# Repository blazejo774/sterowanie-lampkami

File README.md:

# 🔴🟢🔵 Sterowanie Lampkami Choinkowymi

Projekt ma sterować serią diod LED, poprzez zmienianie ustawień diód na jedno z wielu ustawień, z których użytkownik może wybrać przystosowane dla niego oświetlenie. Projekt zaweria różne rodzaje oświetlenia, miedzy innymi:

- [ ] Oscylacja światełek czerwonych, zielonych lub niebieskich.
- [ ] Włączenie bądź wyłączenie poszczególnych kolorów.
- [ ] Inne niestandardowe ustawienia oświetlenia.

Można rozszerzyć ilość używanych diod, poprzez dodanie więcej gałęzi po 3 diody:
 - Zamiast 1 gałęzi z 3 diodami, tworzysz np. 7 równoległych gałęzi po 3 diody w szeregu.
 - Każda gałąź dostaje swój rezystor, np. 7 rezystorów po 120Ω dla zielonych LED-ów.
 - MOSFET steruje wszystkimi 7 gałęziami naraz.
 
👉 Zalety: Nie zmienia się napięcie, MOSFET łatwo steruje większą ilością diod.

## 📝 Dokumentacja

ℹ Kod → [**Dokumentacja**](https://github.com/blazejo774/sterowanie-lampkami/blob/d19fd1ce32649a07414ba25e057f50cffe792c03/%5BCODE%5D/main.c)

ℹ Wykaz elementów → [**Dokumentacja**](https://github.com/blazejo774/sterowanie-lampkami/blob/d19fd1ce32649a07414ba25e057f50cffe792c03/%5BELECTRONICS%5D/readme.md)

## ⭐ Software

💾 Kod → [**main.c**](https://github.com/blazejo774/sterowanie-lampkami/blob/d19fd1ce32649a07414ba25e057f50cffe792c03/%5BCODE%5D/main.c)

## 💡 Hardware

💾 Schemat Elektryczny → [**Schemat Elektryczny**](https://github.com/blazejo774/sterowanie-lampkami/blob/d19fd1ce32649a07414ba25e057f50cffe792c03/%5BELECTRONICS%5D/scheme.pdf)

💾 Schemat Płytki PCB TOP → [**Płytka-TOP**](https://github.com/blazejo774/sterowanie-lampkami/blob/d19fd1ce32649a07414ba25e057f50cffe792c03/%5BBOARD%5D/Board_TOP.pdf)

💾 Schemat Płytki PCB BOTTOM → [**Płytka-BOTTOM**](https://github.com/blazejo774/sterowanie-lampkami/blob/d19fd1ce32649a07414ba25e057f50cffe792c03/%5BBOARD%5D/Board_BOTTOM.pdf)

💾 Schemat Płytki PCB(IMAGE) → [**Płytka**](https://github.com/blazejo774/sterowanie-lampkami/blob/d19fd1ce32649a07414ba25e057f50cffe792c03/%5BBOARD%5D/BOARD.png)

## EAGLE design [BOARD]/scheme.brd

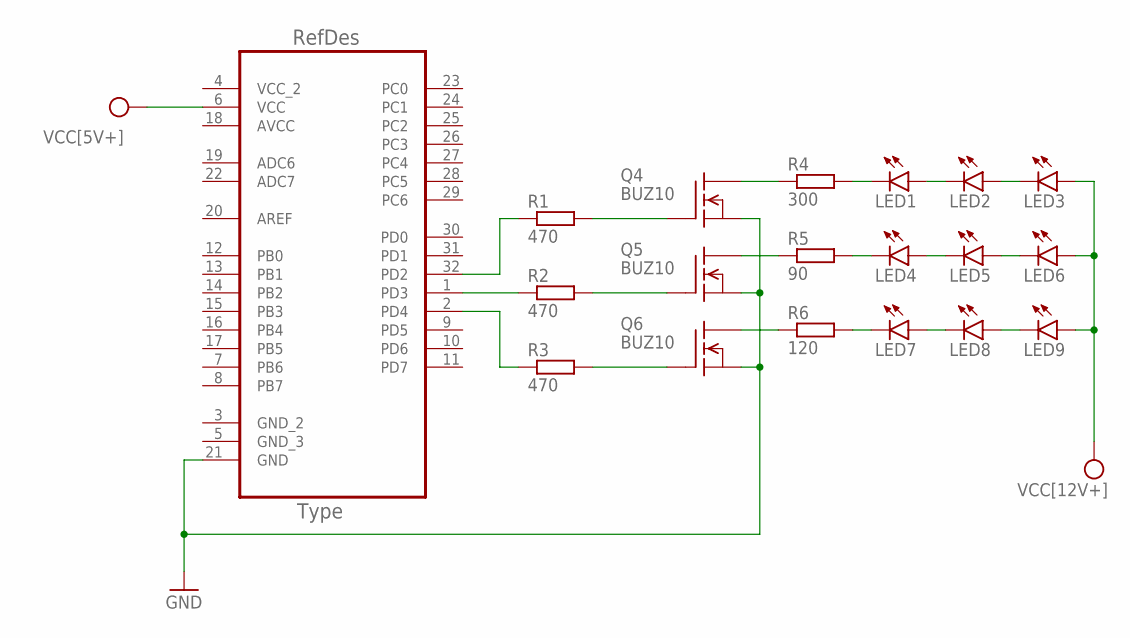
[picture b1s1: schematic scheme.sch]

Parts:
LED1, LED2, LED3, LED4, LED5, LED6, LED7, LED8, LED9: LED5MM
Q4, Q5, Q6: BUZ10; TO220
R1, R2, R3: 470; 0204/7
R4: 300; 0204/7
R5: 90; 0204/7
R6: 120; 0204/7
U2: ATMEGA328P-AU; QFP80P900X900X120-32N

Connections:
AVCC: U2.18 (AVCC)
GND: Q4.3 (S), Q5.3 (S), Q6.3 (S), U2.21 (GND)
unnamed: LED4.K (C), R5.2
unnamed: LED4.A, LED5.K (C)
unnamed: LED1.K (C), R4.2
unnamed: LED1.A, LED2.K (C)
unnamed: LED2.A, LED3.K (C)
unnamed: LED5.A, LED6.K (C)
unnamed: LED7.K (C), R6.2
unnamed: LED7.A, LED8.K (C)
unnamed: LED8.A, LED9.K (C)
unnamed: Q6.2 (D), R6.1
unnamed: Q5.2 (D), R5.1
unnamed: Q4.2 (D), R4.1
unnamed: Q4.1 (G), R1.2
unnamed: Q5.1 (G), R2.2
unnamed: Q6.1 (G), R3.2
unnamed: R2.1, U2.1 (PD3)
unnamed: R3.1, U2.2 (PD4)
unnamed: R1.1, U2.32 (PD2)
VCC: LED3.A, LED6.A, LED9.A, U2.6 (VCC)
VCC_2: U2.4 (VCC_2)

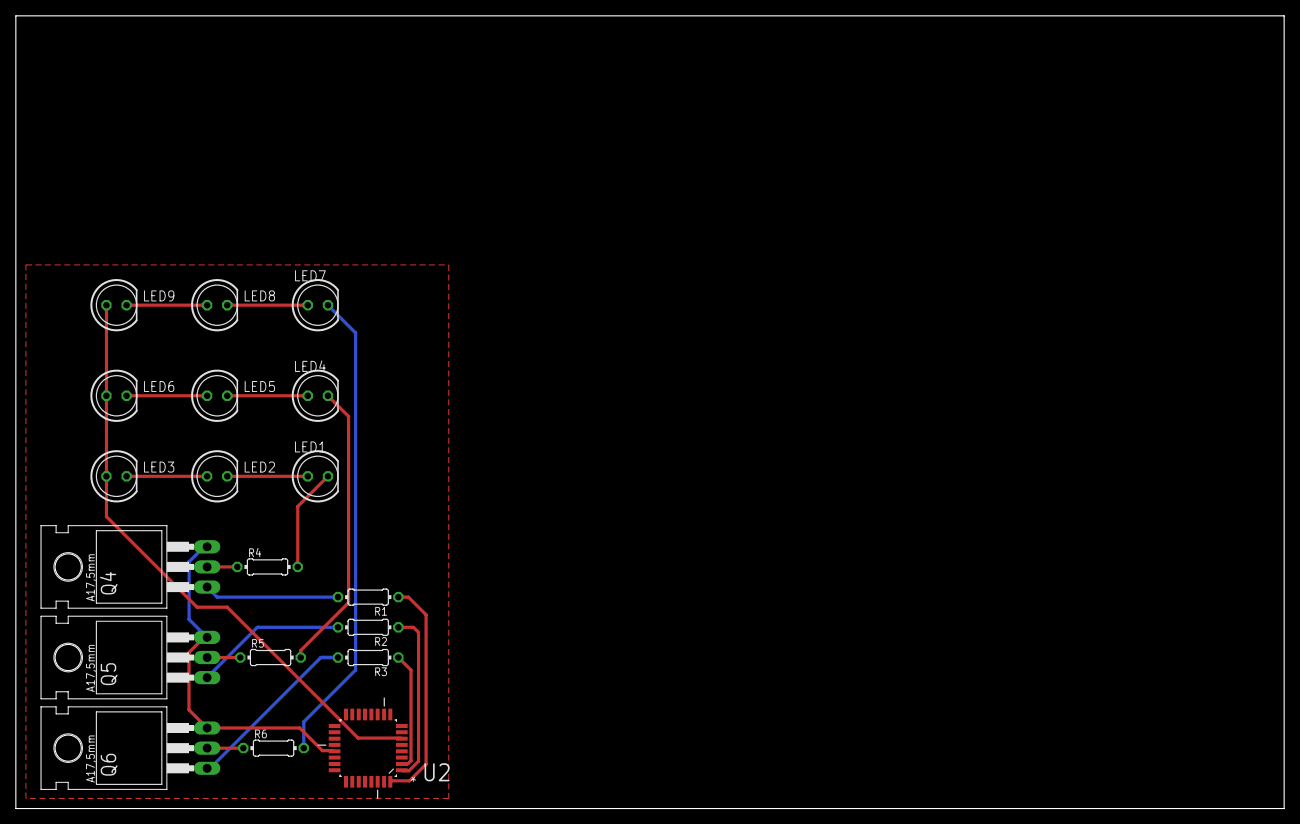
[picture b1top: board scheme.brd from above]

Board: 2 copper layers, 160.0 x 100.0 mm, 19 parts (0 on the bottom side), 20 nets.

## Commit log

2025-03-18 All Files
2025-03-18 Add README.md
